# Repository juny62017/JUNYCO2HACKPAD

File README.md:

This Hackpad is a custom 5-key macropad built using the Seeed XIAO RP2040.
It includes per-key SK6812 MINI reverse-mount RGB LEDs, a rotary encoder, and a 0.91" OLED display.

I built this macropad to make my daily work easier. 
I use a lot of shortcuts and wanted a small device where I can press one button instead of remembering key combinations.
This project helped me understand how hardware and software work together.

I made macropad to make my daily workflow smoother by giving me singlee press access to shortcuts and custom actions I use often, instead of complex keyboard combinations. It was also a personal learning project to improve my skills in PCB design, microcontroller integration, LED routing, and 3D case design.

To use it, just flash the firmware to the XIAO RP2040 and connect it to your computer with a USB cable. The keys can be programmed for shortcuts or macros, and the rotary encoder can control things like volume.

| Component               | Quantity | Specification              | Unit Price | Total Price |
|--------------------------|----------|----------------------------|------------|-------------|
| XIAO RP2040              | 1        | Microcontroller            | $14.60     | $14.60      |
| SK6812MINI-E REV         | 6        | Addressable RGB LEDs      | $2.87      | $17.19      |
| Red Mechanical Switches  | 5        | Keyboard Switches         | $1.21      | $6.05       |
| EC11 Rotary Encoder      | 1        | Encoder with Push Switch  | $0.60      | $0.60       |
| 0.91" OLED Display       | 1        | I2C Display               | $1.65      | $1.65       |
| 220Ω Resistor            | 1        | THT Axial (DIN0207)       | $0.02      | $0.02       |
| Blank DSA Keycaps        | 5        | Keycaps                   | $0.30      | $1.50       |

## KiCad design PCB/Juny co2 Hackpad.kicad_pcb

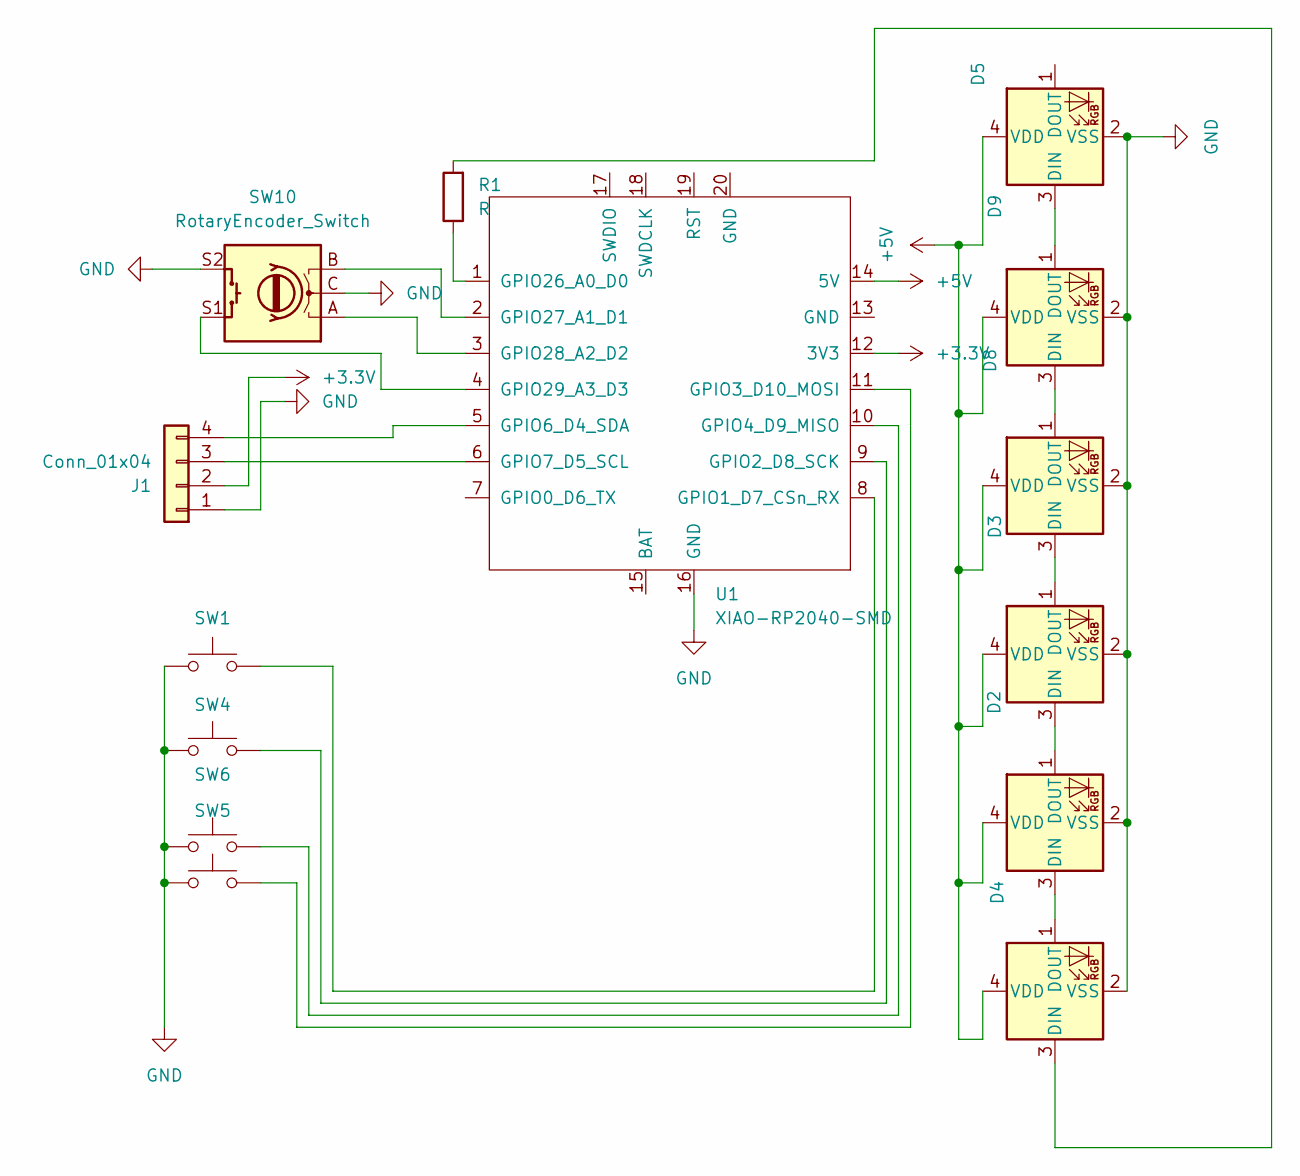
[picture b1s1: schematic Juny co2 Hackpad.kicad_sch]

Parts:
D2, D3, D4, D5, D8, D9: SK6812MINI; LED_SK6812MINI_PLCC4_3.5x3.5mm_P1.75mm
J1: Conn_01x04; PinHeader_1x04_P2.54mm_Vertical
R1: R; R_Axial_DIN0207_L6.3mm_D2.5mm_P10.16mm_Horizontal
SW1, SW4, SW5, SW6: SW_Push; SW_Cherry_MX_1.00u_PCB
SW10: RotaryEncoder_Switch; RotaryEncoder_Alps_EC11E-Switch_Vertical_H20mm
U1: XIAO-RP2040-SMD

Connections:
+3.3V: J1.2, U1.12 (3V3)
+5V: D2.4 (VDD), D3.4 (VDD), D4.4 (VDD), D5.4 (VDD), D8.4 (VDD), D9.4 (VDD), U1.14 (5V)
GND: D2.2 (VSS), D3.2 (VSS), D4.2 (VSS), D5.2 (VSS), D8.2 (VSS), D9.2 (VSS), J1.1, SW1.1, SW4.1, SW5.1, SW6.1, SW10.C, SW10.S2, U1.16 (GND)
unnamed: D2.3 (DIN), D4.1 (DOUT)
unnamed: D2.1 (DOUT), D3.3 (DIN)
unnamed: D3.1 (DOUT), D8.3 (DIN)
unnamed: D4.3 (DIN), R1.2
unnamed: D5.3 (DIN), D9.1 (DOUT)
unnamed: D8.1 (DOUT), D9.3 (DIN)
unnamed: J1.3, U1.6 (GPIO7_D5_SCL)
unnamed: J1.4, U1.5 (GPIO6_D4_SDA)
unnamed: SW1.2, U1.8 (GPIO1_D7_CSn_RX)
unnamed: SW4.2, U1.9 (GPIO2_D8_SCK)
unnamed: SW5.2, U1.11 (GPIO3_D10_MOSI)
unnamed: SW6.2, U1.10 (GPIO4_D9_MISO)
unnamed: R1.1, U1.1 (GPIO26_A0_D0)
unnamed: SW10.B, U1.2 (GPIO27_A1_D1)
unnamed: SW10.A, U1.3 (GPIO28_A2_D2)
unnamed: SW10.S1, U1.4 (GPIO29_A3_D3)

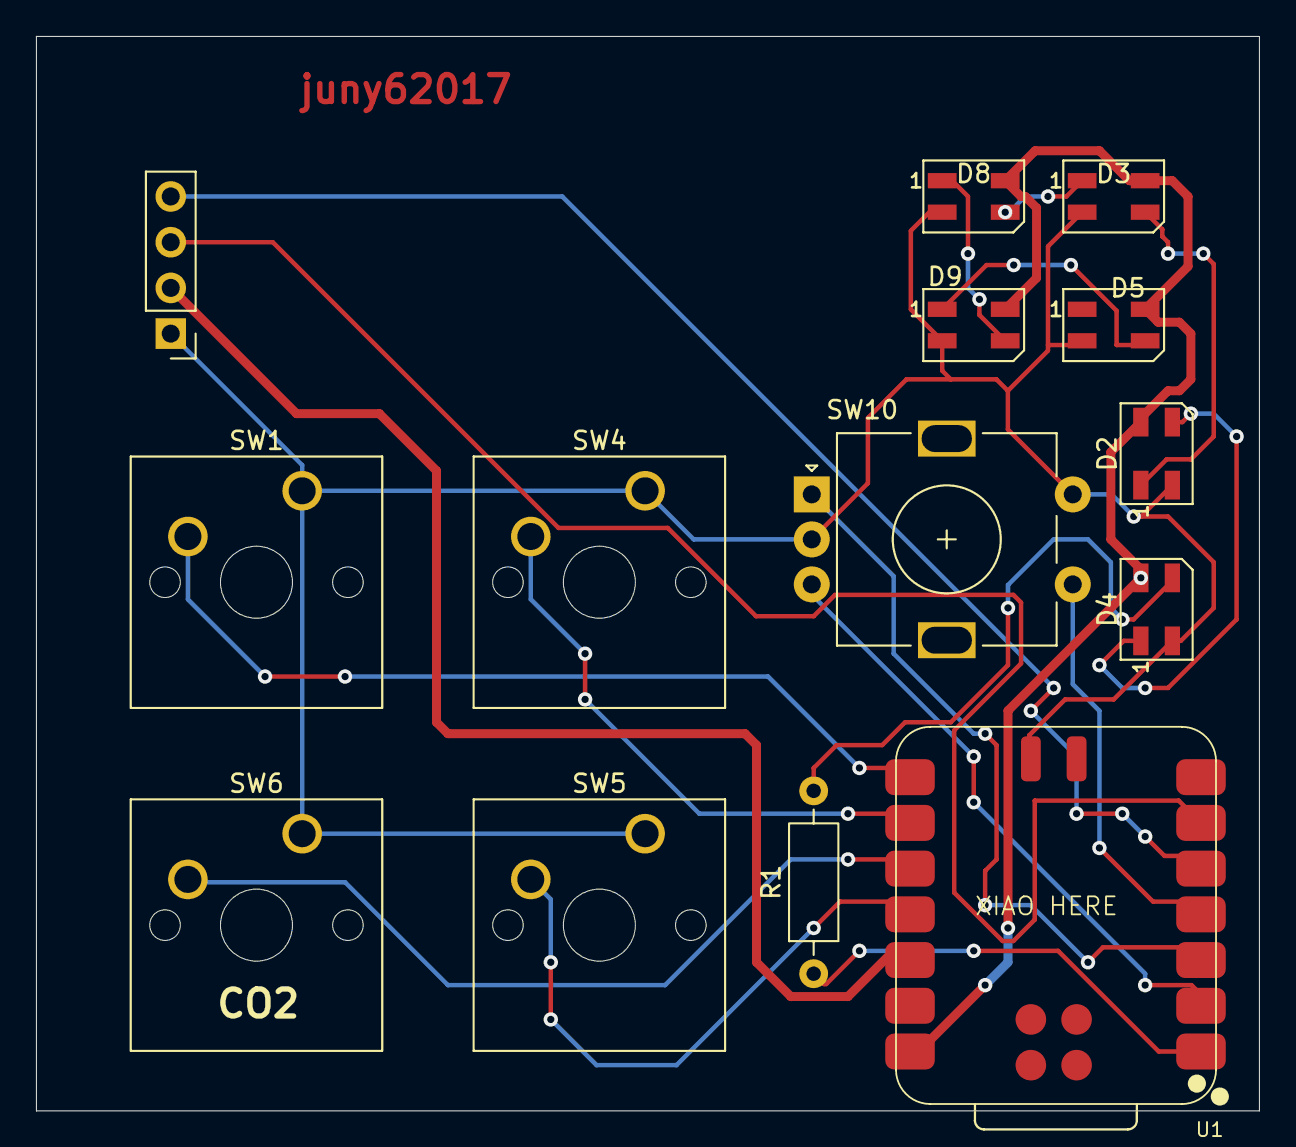
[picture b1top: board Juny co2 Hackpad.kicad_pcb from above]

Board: 2 copper layers, 67.9 x 59.7 mm, 14 parts (0 on the bottom side), 19 nets.
